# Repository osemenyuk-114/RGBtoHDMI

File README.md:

<!-- markdownlint-disable-file MD033 -->
# RGBtoHDMI Hardware Variations & Replicas

This repository contains fully open-source hardware designs, KiCad schematics, PCB layouts, manufacturing files, and Bills of Materials (BOM) for the **RGBtoHDMI** ecosystem.

**RGBtoHDMI** converts pixel-synchronous digital and analog video from vintage computers (Commodore Amiga, Atari ST, BBC Micro, Commodore 64/128, Sinclair ZX Spectrum, IBM PC MDA/CGA/EGA, Apple II, etc.) to clean HDMI using a Raspberry Pi Zero, custom bare-metal firmware, and a CPLD.

---

## 📋 Included Board Designs

### 1. CPLD Hat V6a (12-Bit Digital RGB Interface)

- **Hybrid V4/V6 Architecture:** Combines the compact design of V6 with enhanced physical durability.
- **SMD Resistor Arrays:** Uses compact `0603 x 4` convex resistor arrays (RN1–RN8) instead of the bulky through-hole arrays from the upstream V4 design.
- **Through-Hole Tactile Switches:** Uses standard, readily available 6 mm through-hole tactile pushbuttons (**Alps Alpine SKHHBVA010**) instead of SMD buttons. This change was directly motivated by real-world repair experience: when the buttons on a commercial V6 board failed, several delicate surface-mount pads tore off during desoldering, and finding identical replacement SMD switches proved difficult. THT switches make soldering, future replacements, and long-term maintenance significantly easier and more robust.
- **Quick Links:** [Schematic (PDF)](Kicad_6Bit/v6a/rgb-to-hdmi.pdf) · [Interactive BOM](Kicad_6Bit/v6a/bom/ibom.html) · [Fabrication Files](Kicad_6Bit/v6a/manufacturing/)

### 2. CPLD Hat V7a (12-Bit Digital RGB Interface, Soft Reset Option)

Based on V6a (same functionality, through-hole switches, SMD resistor arrays, same BOM) with a choice of reset wiring. Assemble **one** of the two variants:

| Variant | P4 | D3 | Reset button behavior |
| :--- | :---: | :---: | :--- |
| **A – V7 replica** | fitted | not fitted | Same as V6a: needs the Raspberry Pi reset mod (via `P4`) |
| **B – Soft reset** | not fitted | fitted | Soft reset on reset button press; no modifications to the Pi required |

- **Context:** In the upstream project, issues 5–7 are SMD-only and sold assembled; issue 6 adds series resistors on the inputs for minimal CPLD protection, and issue 7 adds the soft reset. Software reset is also possible on earlier issues by pressing SW1 & SW3.
- **Quick Links:** [Schematic (PDF)](Kicad_6Bit/v7a/rgb-to-hdmi.pdf) · [Interactive BOM](Kicad_6Bit/v7a/bom/ibom.html) · [Fabrication Files](Kicad_6Bit/v7a/manufacturing/)

### 3. HDMI Audio Adapter V2a (Audio Add-on Replica)

- **100% Open Hardware Clean-Room Reverse Engineering:** The audio add-on was previously only distributed as closed commercial hardware without public schematics or Gerber files. This replica brings the hardware back into the open-source community. See also the related [RGBtoHDMI Open Audio project](https://github.com/drdpj/RGBtoHDMI-Open-Audio).
- **Plug-and-Play:** Stacks directly onto header `P2` of the CPLD Hat to feed digital I2S audio into the Raspberry Pi Zero for embedding into the HDMI stream.
- **Quick Links:** [Schematic (PDF)](Kicad_Audio_Adapter/v2a/rgbtohdmi-audio.pdf) · [Interactive BOM](Kicad_Audio_Adapter/v2a/bom/ibom.html) · [Fabrication Files](Kicad_Audio_Adapter/v2a/manufacturing/)

### 4. Analog Board V3a (Analog RGB/YUV Add-on)

- **Cost-Optimized Design:** Compared with the upstream [V3 analog board](https://github.com/IanSB/RGBtoHDMI/tree/master/kicad_analog_6bit/V3), this revision replaces the expensive and hard-to-source `MAX9144` quad comparators with accessible, cost-effective `TLV3512DGKR` dual comparators.
- **⚠️ Untested:** This board has not been built or tested yet. The `TLV3512DGKR` comparators are much faster than the original `MAX9144` (about 6 ns vs. about 40 ns) and are comparable to the `GS8743` used on the V4 analog board (about 6 ns, 3 mV hysteresis). Build at your own risk.
- **Quick Links:** [Schematic (PDF)](Kicad_Analog_6bit/V3a/analog.pdf) · [Interactive BOM](Kicad_Analog_6bit/V3a/bom/ibom.html) · [Fabrication Files](Kicad_Analog_6bit/V3a/manufacturing/)

---

## 🏭 PCB Fabrication Guide (JLCPCB / PCBWay)

Pre-generated, verified manufacturing files (Gerbers and Excellon drill files) are available in each board's `manufacturing/` directory.

To order:

1. Zip the files in the respective board's `manufacturing/` directory.
2. Upload the `.zip` archive to your preferred PCB fabricator (e.g., JLCPCB, PCBWay, OSH Park).
3. Recommended fabrication settings:

| Parameter | Recommended Specification |
| :--- | :--- |
| **Layers** | 2 Layers |
| **Base Material** | Standard FR4 |
| **PCB Thickness** | **1.6 mm** for CPLD Hat V6a/V7a & Analog Board V3a<br>**0.8 mm** for HDMI Audio Adapter V2a |
| **Copper Weight** | 1 oz (35 µm) |
| **Surface Finish** | **ENIG** (recommended for fine-pitch packages: PCM1808 TSSOP-14, XC9572XL VQFP-44) or **Lead-Free HASL** |
| **Solder Mask** | Green (or preferred color) |
| **Silkscreen** | White |

---

## 📖 Software & Documentation

- **Firmware & Releases:** Download pre-built SD card images from the [upstream RGBtoHDMI Releases](https://github.com/IanSB/RGBtoHDMI/releases).
- **User Guide & Wiki:** Comprehensive documentation, configuration instructions, cabling guides, and supported computer profiles can be found on the [official upstream RGBtoHDMI Wiki](https://github.com/IanSB/RGBtoHDMI/wiki).
- **Audio Configuration:** In the RGBtoHDMI on-screen menu, navigate to the audio settings menu to enable HDMI audio embedding.
- **Upstream Sourcing Info:** See upstream [12-bit board BOM](https://github.com/IanSB/RGBtoHDMI/wiki/Bill-of-Materials-%2812-Bit-Board) and [HDMI Audio documentation](https://github.com/IanSB/RGBtoHDMI/wiki/Audio).

---

## 🔍 Interactive BOMs

Interactive HTML assembly guides allow you to easily highlight component placements and trace pads in your web browser:

- 🔗 **CPLD Hat V6a:** [Kicad_6Bit/v6a/bom/ibom.html](Kicad_6Bit/v6a/bom/ibom.html)
- 🔗 **CPLD Hat V7a:** [Kicad_6Bit/v7a/bom/ibom.html](Kicad_6Bit/v7a/bom/ibom.html)
- 🔗 **HDMI Audio Adapter V2a:** [Kicad_Audio_Adapter/v2a/bom/ibom.html](Kicad_Audio_Adapter/v2a/bom/ibom.html)
- 🔗 **Analog Board V3a:** [Kicad_Analog_6bit/V3a/bom/ibom.html](Kicad_Analog_6bit/V3a/bom/ibom.html)

---

## 📊 Detailed Bills of Materials (BOM)

### BOM: CPLD Hat [V6a](Kicad_6Bit/v6a) / [V7a](Kicad_6Bit/v7a)

<table width="100%">
  <thead>
    <tr>
      <th width="20%" align="left">Ref Des</th>
      <th width="35%" align="left">Value</th>
      <th width="10%" align="center">Quantity</th>
      <th width="35%" align="left">Package</th>
    </tr>
  </thead>
  <tbody>
    <tr><th colspan="4" align="left">Semiconductors</th></tr>
    <tr><td>U1</td><td>XC9572XL-VQFP44</td><td align="center">1</td><td>LQFP-44, 10 x 10 mm, 0.8 mm pitch</td></tr>
    <tr><td>D1, D2</td><td>LED 3mm</td><td align="center">2</td><td>3 mm through-hole LED</td></tr>
    <tr><td>D3 <sup>(V7a only)</sup></td><td>BAV70</td><td align="center">1</td><td>SOT-23 (see note below)</td></tr>
    <tr><th colspan="4" align="left">Resistors</th></tr>
    <tr><td>R1, R2, R3, R4, R5, R6</td><td>1K</td><td align="center">6</td><td>0603 (1608 metric), SMD</td></tr>
    <tr><td>RN1, RN2, RN3, RN4</td><td>4K7</td><td align="center">4</td><td>4 x 0603 resistor array (Convex)</td></tr>
    <tr><td>RN5, RN6, RN7, RN8</td><td>22R</td><td align="center">4</td><td>4 x 0603 resistor array (Convex)</td></tr>
    <tr><th colspan="4" align="left">Capacitors</th></tr>
    <tr><td>C1</td><td>10uF</td><td align="center">1</td><td>0805 (2012 metric), SMD</td></tr>
    <tr><td>C2, C3, C4</td><td>100nF</td><td align="center">3</td><td>0805 (2012 metric), SMD</td></tr>
    <tr><th colspan="4" align="left">Switches</th></tr>
    <tr><td>SW1, SW2, SW3, SW4</td><td>Alps Alpine<br>SKHHBVA010</td><td align="center">4</td><td>6 mm tactile pushbutton, THT</td></tr>
    <tr><th colspan="4" align="left">Sockets / Connectors</th></tr>
    <tr><td>P1</td><td>Wurth Elektronik<br>61304021821</td><td align="center">1</td><td>2 x 20, 2.54 mm socket, vertical</td></tr>
    <tr><td>P2</td><td>Samtec<br>TSW-106-08-L-D-RA</td><td align="center">1</td><td>2 x 6, 2.54 mm pin header, right-angle</td></tr>
    <tr><td>P4 <sup>(V7a: variant A only)</sup></td><td>Wurth Elektronik<br>61300211821</td><td align="center">1</td><td>1 x 2, 2.54 mm socket, vertical</td></tr>
    <tr><td>P5</td><td>Samtec<br>SLW-105-01-T-D</td><td align="center">1</td><td>2 x 5, 2.54 mm socket, vertical</td></tr>
  </tbody>
</table>

> **Note (D3, V7a only):** Fit D3 (BAV70, SOT-23) only for the soft-reset variant B, and then leave P4 unpopulated. For variant A (V7 replica) fit P4 and omit D3. V6a has neither D3 nor the variant choice (P4 is always fitted).

---

### BOM: [HDMI Audio Adapter V2a](Kicad_Audio_Adapter/v2a)

<table width="100%">
  <thead>
    <tr>
      <th width="20%" align="left">Ref Des</th>
      <th width="35%" align="left">Value</th>
      <th width="10%" align="center">Quantity</th>
      <th width="35%" align="left">Package</th>
    </tr>
  </thead>
  <tbody>
    <tr><th colspan="4" align="left">Semiconductors</th></tr>
    <tr><td>U1</td><td>PCM1808PWR</td><td align="center">1</td><td>TSSOP-14, 4.4 x 5 mm, 0.65 mm pitch</td></tr>
    <tr><td>U2</td><td>74LVC1G157</td><td align="center">1</td><td>SOT-363 (SC-70-6)</td></tr>
    <tr><td>U3, U4, U5</td><td>74LVC1G80</td><td align="center">3</td><td>SOT-353 (SC-70-5)</td></tr>
    <tr><th colspan="4" align="left">Resistors</th></tr>
    <tr><td>R1, R2</td><td>470R</td><td align="center">2</td><td>0603 (1608 metric), SMD</td></tr>
    <tr><td>R3, R5, R6</td><td>560R</td><td align="center">3</td><td>0603 (1608 metric), SMD</td></tr>
    <tr><td>R4, R7</td><td>4K7</td><td align="center">2</td><td>0603 (1608 metric), SMD</td></tr>
    <tr><th colspan="4" align="left">Capacitors</th></tr>
    <tr><td>C1, C2</td><td>1uF</td><td align="center">2</td><td>0603 (1608 metric), SMD</td></tr>
    <tr><td>C3, C4, C12</td><td>10uF</td><td align="center">3</td><td>0603 (1608 metric), SMD</td></tr>
    <tr><td>C6, C7</td><td>10nF</td><td align="center">2</td><td>0603 (1608 metric), SMD</td></tr>
    <tr><td>C5, C8, C9, C10, C11</td><td>0.1uF</td><td align="center">5</td><td>0603 (1608 metric), SMD</td></tr>
    <tr><th colspan="4" align="left">Oscillator</th></tr>
    <tr><td>Y1</td><td>12.288 MHz</td><td align="center">1</td><td>SMD oscillator, 4-pad, 3.2 x 2.5 mm</td></tr>
  </tbody>
</table>

---

### BOM: [Analog Board V3a](Kicad_Analog_6bit/V3a)

<table width="100%">
  <thead>
    <tr>
      <th width="20%" align="left">Ref Des</th>
      <th width="35%" align="left">Value</th>
      <th width="10%" align="center">Quantity</th>
      <th width="35%" align="left">Package</th>
    </tr>
  </thead>
  <tbody>
    <tr><th colspan="4" align="left">Semiconductors</th></tr>
    <tr><td>D1</td><td>MBR130LSFT1G</td><td align="center">1</td><td>SOD-123</td></tr>
    <tr><td>U1, U2, U3, U4, U5</td><td>TLV3512DGKR</td><td align="center">5</td><td>VSSOP-8 (DGK), 0.65 mm pitch</td></tr>
    <tr><td>U6</td><td>TS5A3159ADBVR</td><td align="center">1</td><td>SOT-23-6</td></tr>
    <tr><td>U7</td><td>74LVC4066</td><td align="center">1</td><td>SOIC-14, 3.9 x 8.7 mm, 1.27 mm pitch</td></tr>
    <tr><td>U8</td><td>MAX5259EEE+</td><td align="center">1</td><td>QSOP-16, 3.9 x 4.9 mm, 0.635 mm pitch</td></tr>
    <tr><td>U9</td><td>MCP1754S-3302xCB</td><td align="center">1</td><td>SOT-23</td></tr>
    <tr><th colspan="4" align="left">Resistors</th></tr>
    <tr><td>R1</td><td>470R</td><td align="center">1</td><td>0805 (2012 metric), SMD</td></tr>
    <tr><td>R2, R3, R4</td><td>1K</td><td align="center">3</td><td>0805 (2012 metric), SMD</td></tr>
    <tr><td>R5</td><td>10K</td><td align="center">1</td><td>0805 (2012 metric), SMD</td></tr>
    <tr><td>R6, R7, R8</td><td>47K</td><td align="center">3</td><td>0805 (2012 metric), SMD</td></tr>
    <tr><td>R9, R10, R11</td><td>75R</td><td align="center">3</td><td>0805 (2012 metric), SMD</td></tr>
    <tr><th colspan="4" align="left">Capacitors</th></tr>
    <tr><td>C1, C2, C3, C4, C5</td><td>100nF</td><td align="center">5</td><td>0805 (2012 metric), SMD</td></tr>
    <tr><td>C6, C7, C8, C9</td><td>10uF</td><td align="center">4</td><td>0805 (2012 metric), SMD</td></tr>
    <tr><th colspan="4" align="left">Sockets / Connectors</th></tr>
    <tr><td>P1</td><td>Samtec<br>SSW-106-02-T-D-RA</td><td align="center">1</td><td>2 x 6, 2.54 mm socket, right-angle</td></tr>
    <tr><td>P2</td><td>Samtec<br>TLW-104-06-T-S</td><td align="center">1</td><td>1 x 4, 2.54 mm pin header, vertical</td></tr>
    <tr><td>P4</td><td>IDC 6 pin</td><td align="center">1</td><td>2 x 3, 2.54 mm pin header, vertical</td></tr>
    <tr><td>P6, P7</td><td>Samtec<br>TLW-101-06-T-S</td><td align="center">2</td><td>1 x 1, 2.54 mm pin header, vertical</td></tr>
  </tbody>
</table>

---

## 📜 License & Acknowledgments

- This project is distributed under the **GNU General Public License v3.0 (GPL-3.0)**. See the [LICENSE](LICENSE) file for details.
- Original RGBtoHDMI design by David Banks ([hoglet67](https://github.com/hoglet67/RGBtoHDMI)).
- Extended development and maintenance by [IanSB](https://github.com/IanSB/RGBtoHDMI).
- Audio reverse-engineering inspiration and insights from [drdpj/RGBtoHDMI-Open-Audio](https://github.com/drdpj/RGBtoHDMI-Open-Audio).

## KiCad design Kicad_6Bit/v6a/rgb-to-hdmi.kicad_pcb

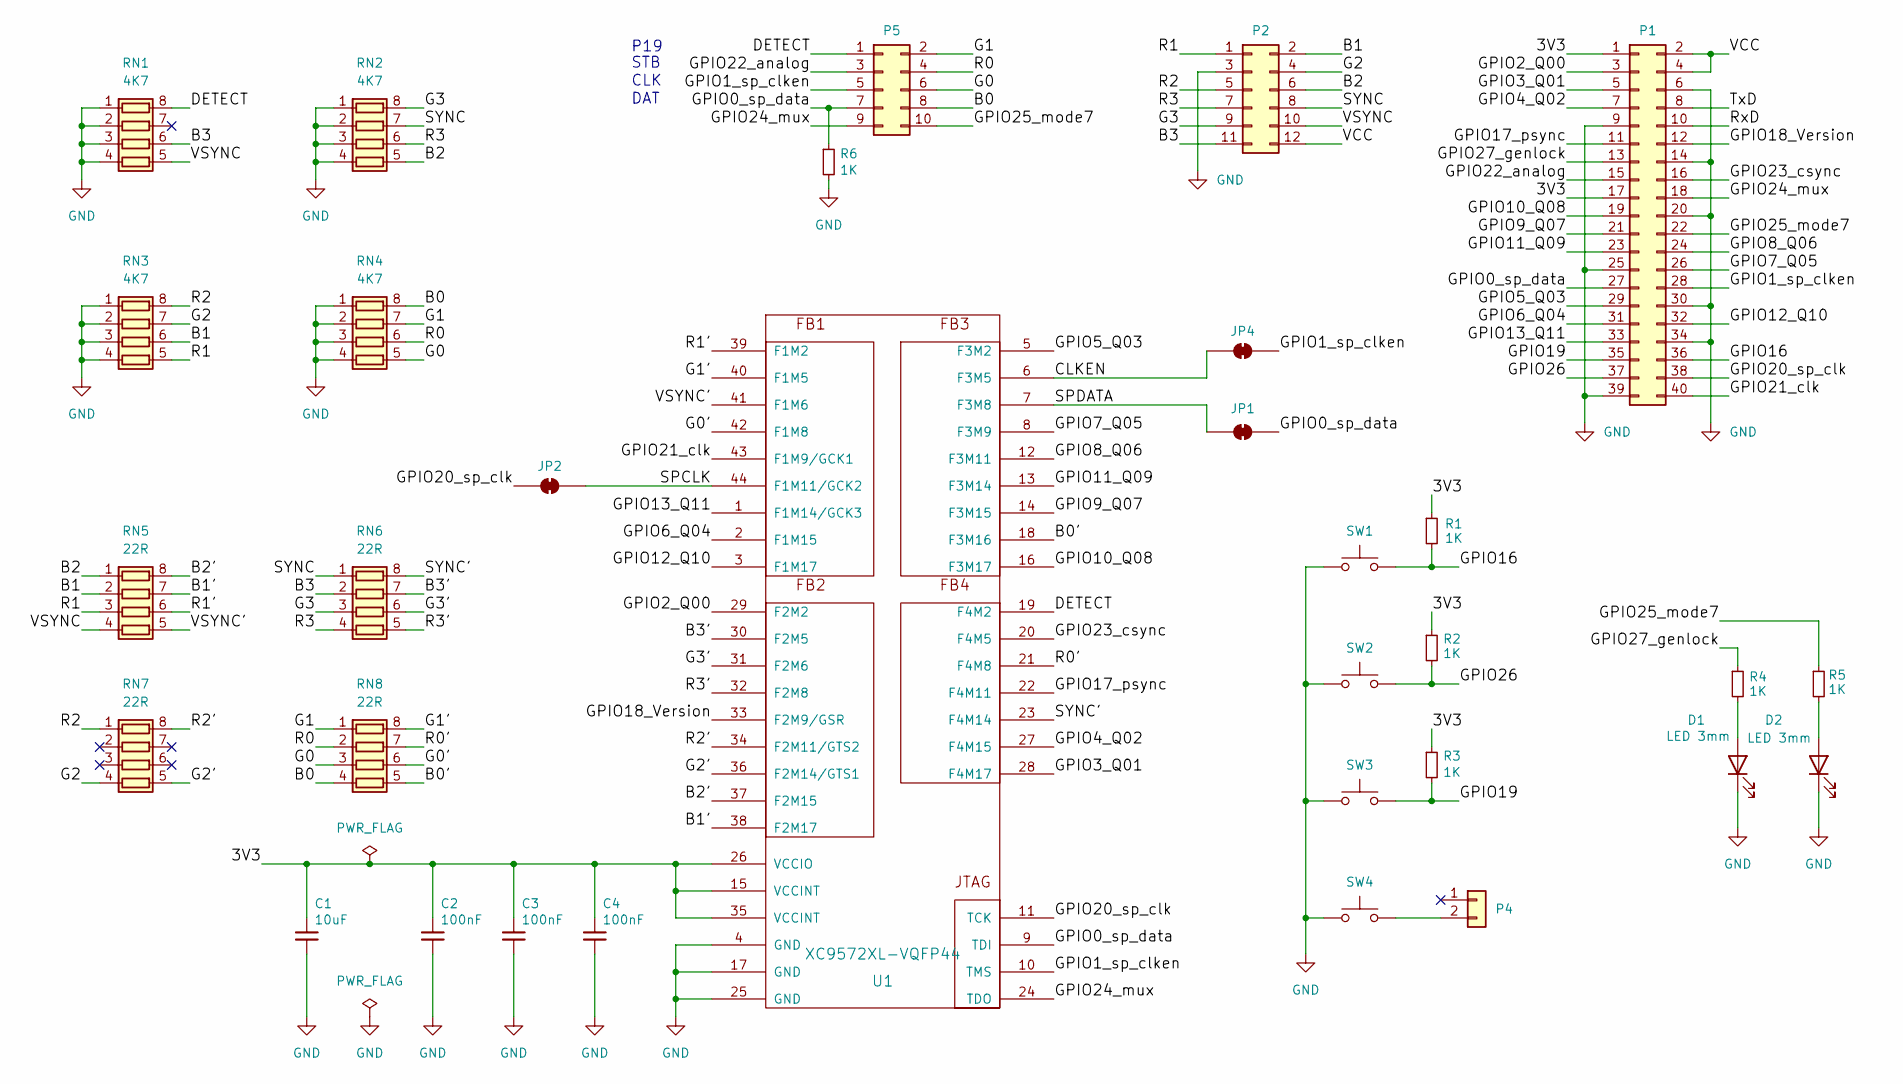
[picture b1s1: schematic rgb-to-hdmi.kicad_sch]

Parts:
C1: 10uF; C_0805_2012Metric_Pad1.18x1.45mm_HandSolder
C2, C3, C4: 100nF; C_0805_2012Metric_Pad1.18x1.45mm_HandSolder
D1, D2: LED 3mm; LED_D3.0mm
JP1, JP2, JP4: Solder Jumper 2 Bridged; SolderJumper-2_P1.3mm_Bridged_RoundedPad1.0x1.5mm
P1: Wurth Elektronik 61304021821; PinSocket_2x20_P2.54mm_Vertical
P2: Samtec TSW-106-08-L-D-RA; PinHeader_2x06_P2.54mm_Horizontal
P4: Wurth Elektronik 61300211821; PinSocket_1x02_P2.54mm_Vertical
P5: Samtec SLW-105-01-T-D; PinSocket_2x05_P2.54mm_Vertical
R1, R2, R3, R4, R5, R6: 1K; R_0603_1608Metric_Pad0.98x0.95mm_HandSolder
RN1, RN2, RN3, RN4: 4K7; R_Array_Convex_4x0603
RN5, RN6, RN7, RN8: 22R; R_Array_Convex_4x0603
SW1, SW2, SW3, SW4: Alps Alpine SKHHBVA010; SW_PUSH_6mm_H7.3mm
U1: XC9572XL-VQFP44; LQFP-44_10x10mm_P0.8mm

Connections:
/3V3: C1.1, C2.1, C3.1, C4.1, P1.1, P1.17, R1.1, R2.1, R3.1, U1.15 (VCCINT), U1.26 (VCCIO), U1.35 (VCCINT)
/B0: P5.8, RN4.8 (R1.2), RN8.4 (R4.1)
/B0': RN8.5 (R4.2), U1.18 (F3M16)
/B1: P2.2, RN3.6 (R3.2), RN5.2 (R2.1)
/B1': RN5.7 (R2.2), U1.38 (F2M17)
/B2: P2.6, RN2.5 (R4.2), RN5.1 (R1.1)
/B2': RN5.8 (R1.2), U1.37 (F2M15)
/B3: P2.11, RN1.6 (R3.2), RN6.2 (R2.1)
/B3': RN6.7 (R2.2), U1.30 (F2M5)
/CLKEN: JP4.2 (B), U1.6 (F3M5)
/DETECT: P5.1, RN1.8 (R1.2), U1.19 (F4M2)
/G0: P5.6, RN4.5 (R4.2), RN8.3 (R3.1)
/G0': RN8.6 (R3.2), U1.42 (F1M8)
/G1: P5.2, RN4.7 (R2.2), RN8.1 (R1.1)
/G1': RN8.8 (R1.2), U1.40 (F1M5)
/G2: P2.4, RN3.7 (R2.2), RN7.4 (R4.1)
/G2': RN7.5 (R4.2), U1.36 (F2M14/GTS1)
/G3: P2.9, RN2.8 (R1.2), RN6.3 (R3.1)
/G3': RN6.6 (R3.2), U1.31 (F2M6)
/GPIO0_sp_data: JP1.1 (A), P1.27, P5.7, R6.1, U1.9 (TDI)
/GPIO1_sp_clken: JP4.1 (A), P1.28, P5.5, U1.10 (TMS)
/GPIO2_Q00: P1.3, U1.29 (F2M2)
/GPIO3_Q01: P1.5, U1.28 (F4M17)
/GPIO4_Q02: P1.7, U1.27 (F4M15)
/GPIO5_Q03: P1.29, U1.5 (F3M2)
/GPIO6_Q04: P1.31, U1.2 (F1M15)
/GPIO7_Q05: P1.26, U1.8 (F3M9)
/GPIO8_Q06: P1.24, U1.12 (F3M11)
/GPIO9_Q07: P1.21, U1.14 (F3M15)
/GPIO10_Q08: P1.19, U1.16 (F3M17)
/GPIO11_Q09: P1.23, U1.13 (F3M14)
/GPIO12_Q10: P1.32, U1.3 (F1M17)
/GPIO13_Q11: P1.33, U1.1 (F1M14/GCK3)
/GPIO16: P1.36, R1.2, SW1.2
/GPIO17_psync: P1.11, U1.22 (F4M11)
/GPIO18_Version: P1.12, U1.33 (F2M9/GSR)
/GPIO19: P1.35, R3.2, SW3.2
/GPIO20_sp_clk: JP2.1 (A), P1.38, U1.11 (TCK)
/GPIO21_clk: P1.40, U1.43 (F1M9/GCK1)
/GPIO22_analog: P1.15, P5.3
/GPIO23_csync: P1.16, U1.20 (F4M5)
/GPIO24_mux: P1.18, P5.9, U1.24 (TDO)
/GPIO25_mode7: P1.22, P5.10, R5.1
/GPIO26: P1.37, R2.2, SW2.2
/GPIO27_genlock: P1.13, R4.1
/R0: P5.4, RN4.6 (R3.2), RN8.2 (R2.1)
/R0': RN8.7 (R2.2), U1.21 (F4M8)
/R1: P2.1, RN3.5 (R4.2), RN5.3 (R3.1)
/R1': RN5.6 (R3.2), U1.39 (F1M2)
/R2: P2.5, RN3.8 (R1.2), RN7.1 (R1.1)
/R2': RN7.8 (R1.2), U1.34 (F2M11/GTS2)
/R3: P2.7, RN2.6 (R3.2), RN6.4 (R4.1)
/R3': RN6.5 (R4.2), U1.32 (F2M8)
/RxD: P1.10
/SPCLK: JP2.2 (B), U1.44 (F1M11/GCK2)
/SPDATA: JP1.2 (B), U1.7 (F3M8)
/SYNC: P2.8, RN2.7 (R2.2), RN6.1 (R1.1)
/SYNC': RN6.8 (R1.2), U1.23 (F4M14)
/TxD: P1.8
/VCC: P1.2, P1.4, P2.12
/VSYNC: P2.10, RN1.5 (R4.2), RN5.4 (R4.1)
/VSYNC': RN5.5 (R4.2), U1.41 (F1M6)
GND: C1.2, C2.2, C3.2, C4.2, D1.1 (K), D2.1 (K), P1.6, P1.9, P1.14, P1.20, P1.25, P1.30, P1.34, P1.39, P2.3, R6.2, RN1.1 (R1.1), RN1.2 (R2.1), RN1.3 (R3.1), RN1.4 (R4.1), RN2.1 (R1.1), RN2.2 (R2.1), RN2.3 (R3.1), RN2.4 (R4.1), RN3.1 (R1.1), RN3.2 (R2.1), RN3.3 (R3.1), RN3.4 (R4.1), RN4.1 (R1.1), RN4.2 (R2.1), RN4.3 (R3.1), RN4.4 (R4.1), SW1.1, SW2.1, SW3.1, SW4.1, U1.4 (GND), U1.17 (GND), U1.25 (GND)
unnamed: D1.2 (A), R4.2
unnamed: D2.2 (A), R5.2
unnamed: P4.2 (Pin_2_2), SW4.2

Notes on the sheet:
DAT
P19
CLK
STB

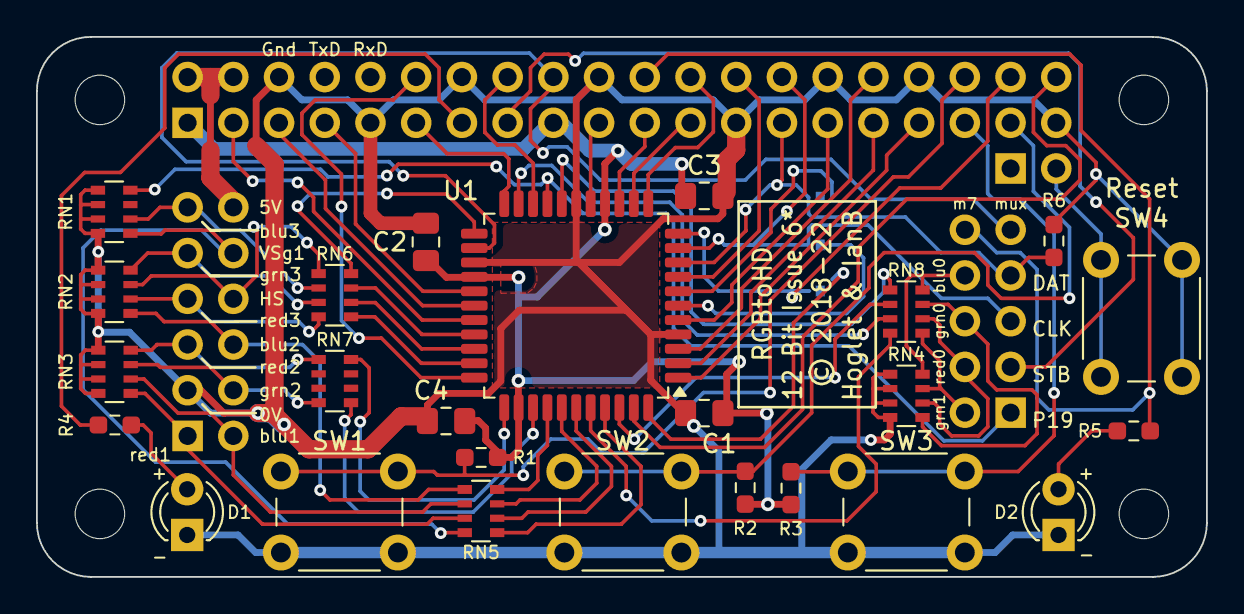
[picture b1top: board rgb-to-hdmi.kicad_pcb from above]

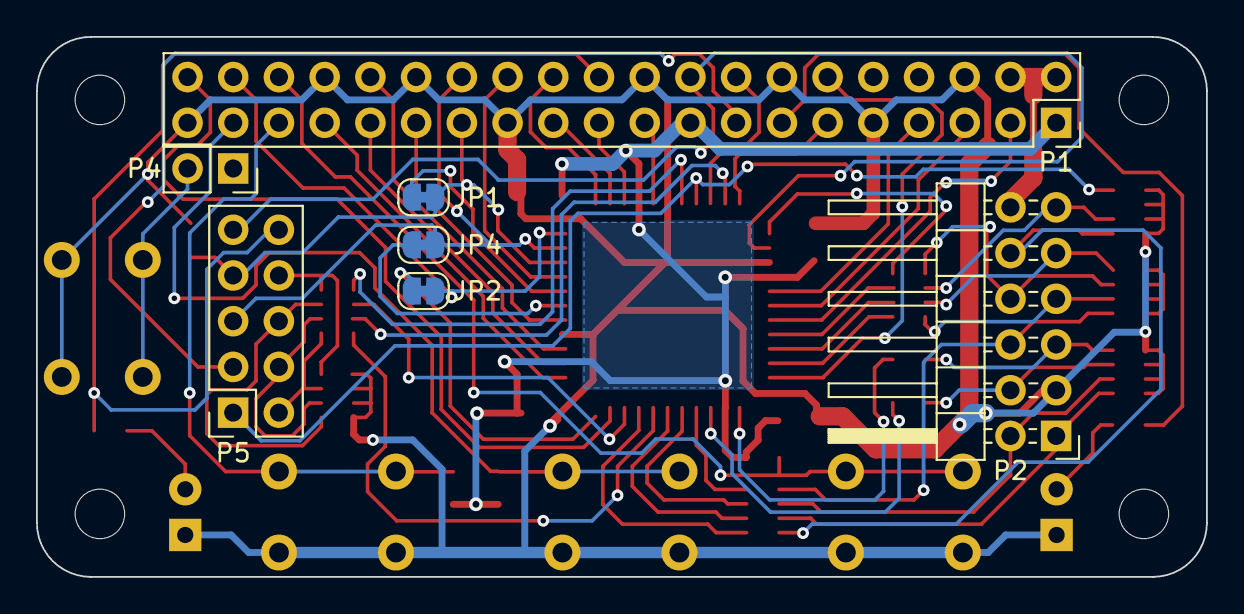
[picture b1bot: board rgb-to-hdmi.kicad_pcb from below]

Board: 2 copper layers, 65.0 x 30.0 mm, 32 parts (7 on the bottom side), 64 nets.

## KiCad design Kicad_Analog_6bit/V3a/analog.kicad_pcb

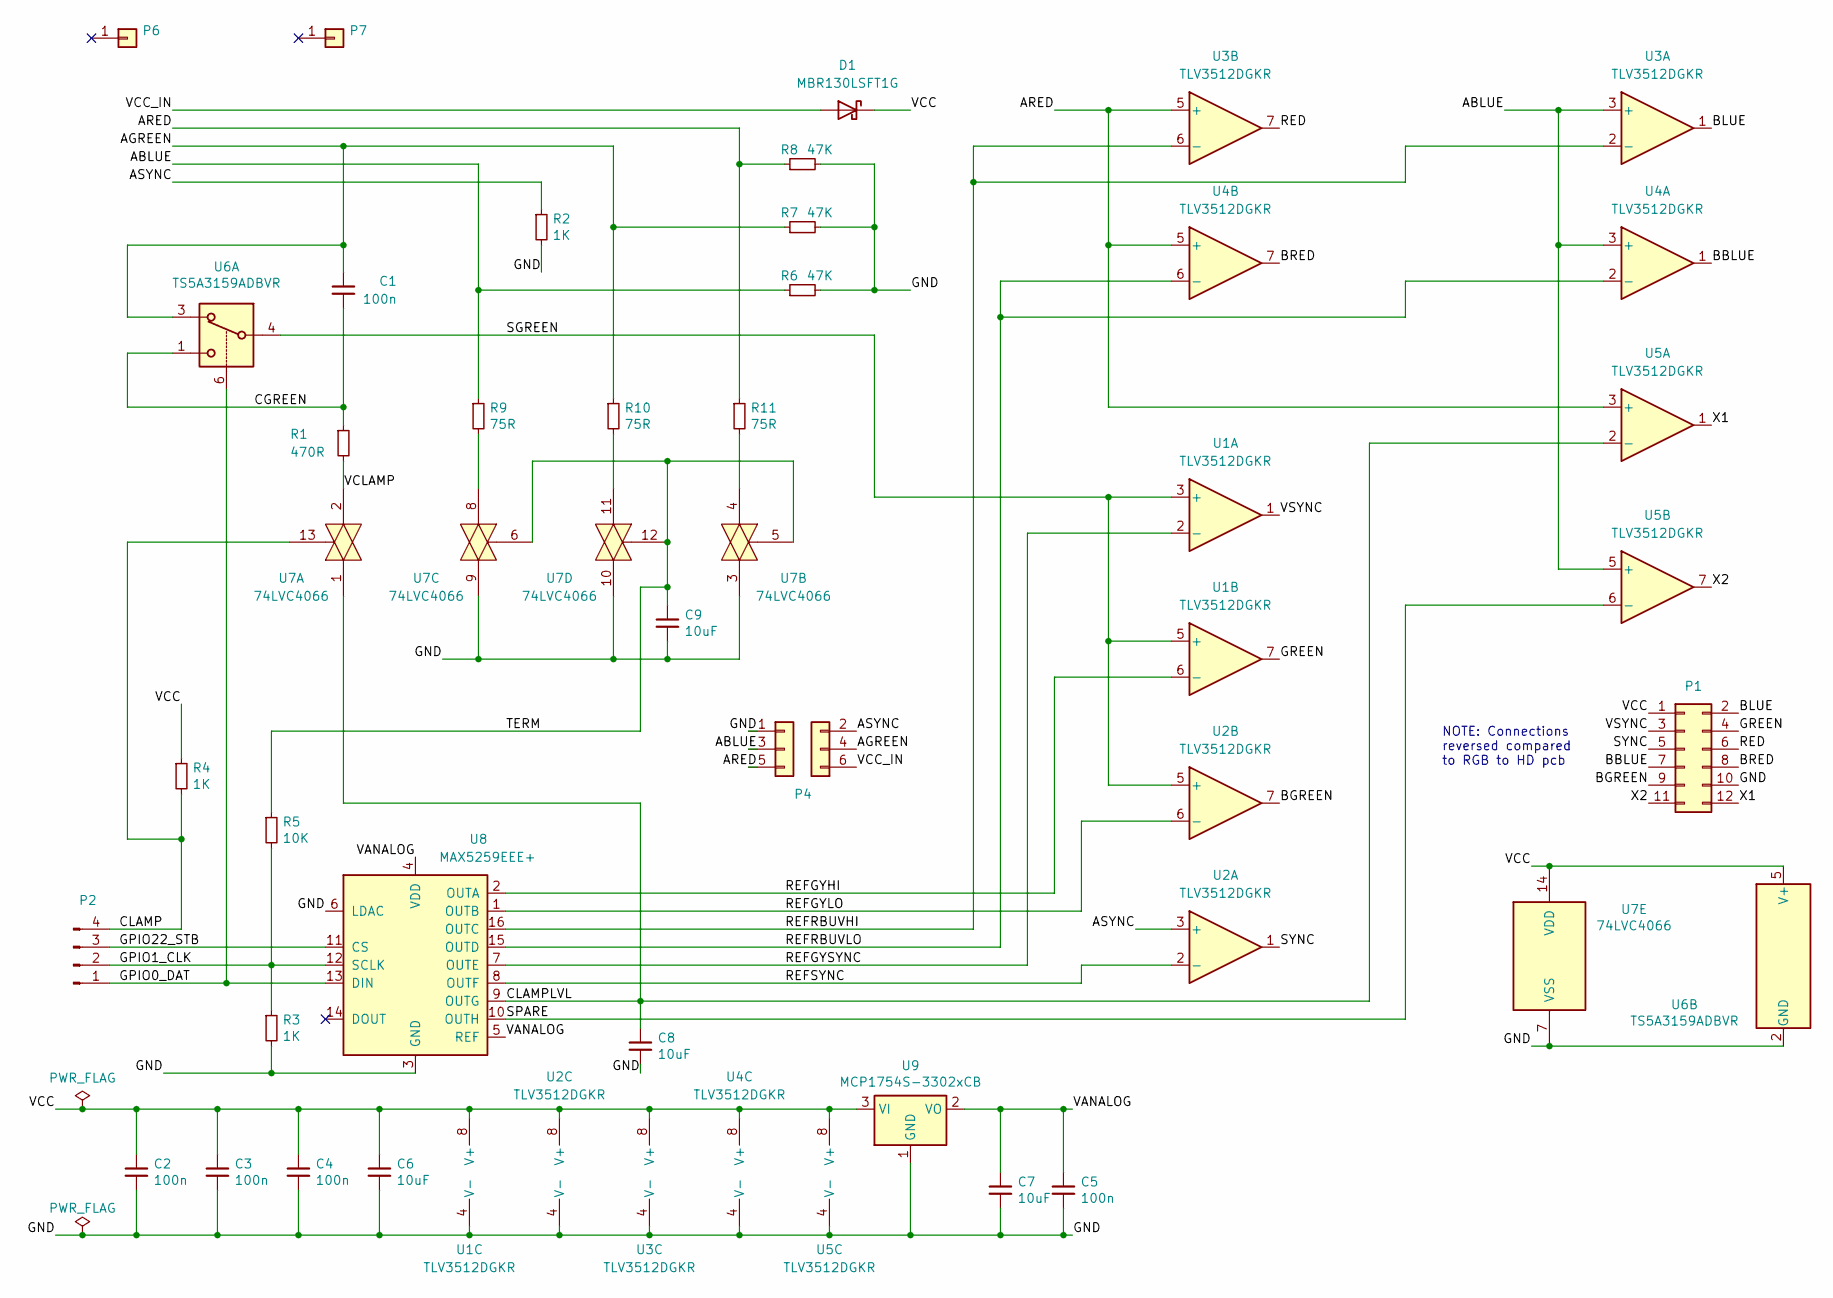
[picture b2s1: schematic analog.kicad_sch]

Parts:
C1, C2, C3, C4, C5: 100n; C_0805_2012Metric_Pad1.18x1.45mm_HandSolder
C6, C7, C8, C9: 10uF; C_0805_2012Metric_Pad1.18x1.45mm_HandSolder
D1: MBR130LSFT1G; D_SOD-123
P1: Samtec SSW-106-02-T-D-RA; PinSocket_2x06_P2.54mm_Horizontal
P2: Samtec TLW-104-06-T-S; PinHeader_1x04_P2.54mm_Vertical
P4: IDC 6pin; Harwin_M20-89003xx_1x03_P2.54mm_Horizontal_Custom_ODD2
P5: Conn_01x03_EVEN; Harwin_M20-89003xx_1x03_P2.54mm_Horizontal_Custom_EVEN2
P6, P7: Samtec TLW-101-06-T-S; PinHeader_1x01_P2.54mm_Vertical
R1: 470R; R_0805_2012Metric_Pad1.20x1.40mm_HandSolder
R2, R3, R4: 1K; R_0805_2012Metric_Pad1.20x1.40mm_HandSolder
R5: 10K; R_0805_2012Metric_Pad1.20x1.40mm_HandSolder
R6, R7, R8: 47K; R_0805_2012Metric_Pad1.20x1.40mm_HandSolder
R9, R10, R11: 75R; R_0805_2012Metric_Pad1.20x1.40mm_HandSolder
U1, U2, U3, U4, U5: TLV3512DGKR; SSOP-8_2.95x2.8mm_P0.65mm
U6: TS5A3159ADBVR; SOT-23-6_Handsoldering
U7: 74LVC4066; SOIC-14_3.9x8.7mm_P1.27mm
U8: MAX5259EEE+; QSOP-16_3.9x4.9mm_P0.635mm
U9: MCP1754S-3302xCB; SOT-23_Handsoldering

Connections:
/ABLUE: P4.3, R6.1, R9.1, U3.3 (+), U4.3 (+), U5.5 (+)
/AGREEN: C1.1, P5.4, R7.1, R10.1, U6.3
/ARED: P4.5, R8.1, R11.1, U3.5 (+), U4.5 (+), U5.3 (+)
/ASYNC: P5.2, R2.1, U2.3 (+)
/BBLUE: P1.7, U4.1
/BGREEN: P1.9, U2.7
/BLUE: P1.2, U3.1
/BRED: P1.8, U4.7
/CGREEN: C1.2, R1.1, U6.1
/CLAMP: P2.4, R4.2, U7.13
/CLAMPLVL: C8.1, U5.2 (-), U7.1, U8.9 (OUTG)
/GND: C2.2, C3.2, C4.2, C5.2, C6.2, C7.2, C8.2, C9.2, P1.10, P4.1, R2.2, R3.2, R6.2, R7.2, R8.2, U1.4 (V-), U2.4 (V-), U3.4 (V-), U4.4 (V-), U5.4 (V-), U6.2 (GND), U7.3, U7.7 (VSS), U7.9, U7.10, U8.3 (GND), U8.6 (LDAC), U9.1 (GND)
/GPIO0_DAT: P2.1, U6.6, U8.13 (DIN)
/GPIO1_CLK: P2.2, R3.1, R5.2, U8.12 (SCLK)
/GPIO22_STB: P2.3, U8.11 (CS)
/GREEN: P1.4, U1.7
/RED: P1.6, U3.7
/REFGYHI: U1.6 (-), U8.2 (OUTA)
/REFGYLO: U2.6 (-), U8.1 (OUTB)
/REFGYSYNC: U1.2 (-), U8.7 (OUTE)
/REFRBUVHI: U3.2 (-), U3.6 (-), U8.16 (OUTC)
/REFRBUVLO: U4.2 (-), U4.6 (-), U8.15 (OUTD)
/REFSYNC: U2.2 (-), U8.8 (OUTF)
/SGREEN: U1.3 (+), U1.5 (+), U2.5 (+), U6.4
/SPARE: U5.6 (-), U8.10 (OUTH)
/SYNC: P1.5, U2.1
/TERM: C9.1, R5.1, U7.5, U7.6, U7.12
/VANALOG: C5.1, C7.1, U8.4 (VDD), U8.5 (REF), U9.2 (VO)
/VCC: C2.1, C3.1, C4.1, C6.1, D1.1 (K), P1.1, R4.1, U1.8 (V+), U2.8 (V+), U3.8 (V+), U4.8 (V+), U5.8 (V+), U6.5 (V+), U7.14 (VDD), U9.3 (VI)
/VCC_IN: D1.2 (A), P5.6
/VCLAMP: R1.2, U7.2
/VSYNC: P1.3, U1.1
/X1: P1.12, U5.1
/X2: P1.11, U5.7
unnamed: R9.2, U7.8
unnamed: R10.2, U7.11
unnamed: R11.2, U7.4

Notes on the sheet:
NOTE: Connections reversed compared to RGB to HD pcb

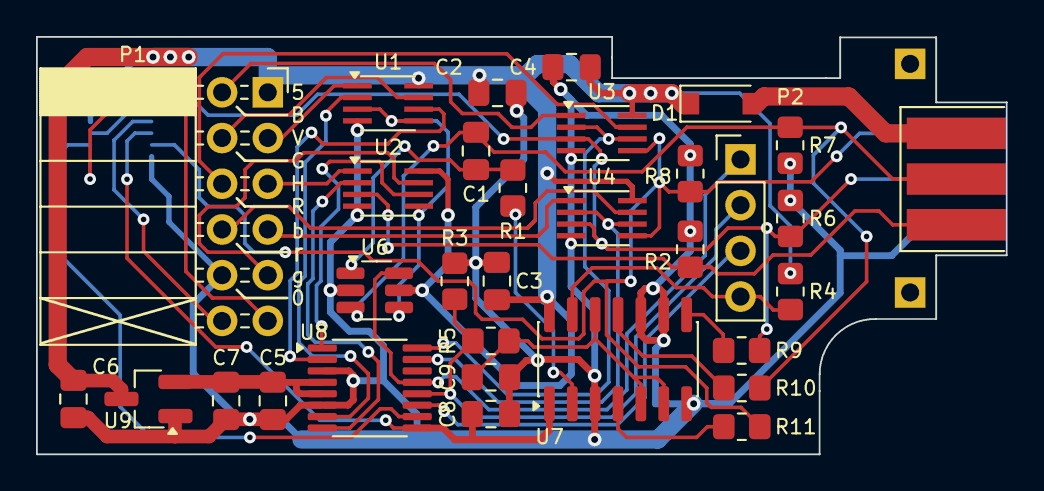
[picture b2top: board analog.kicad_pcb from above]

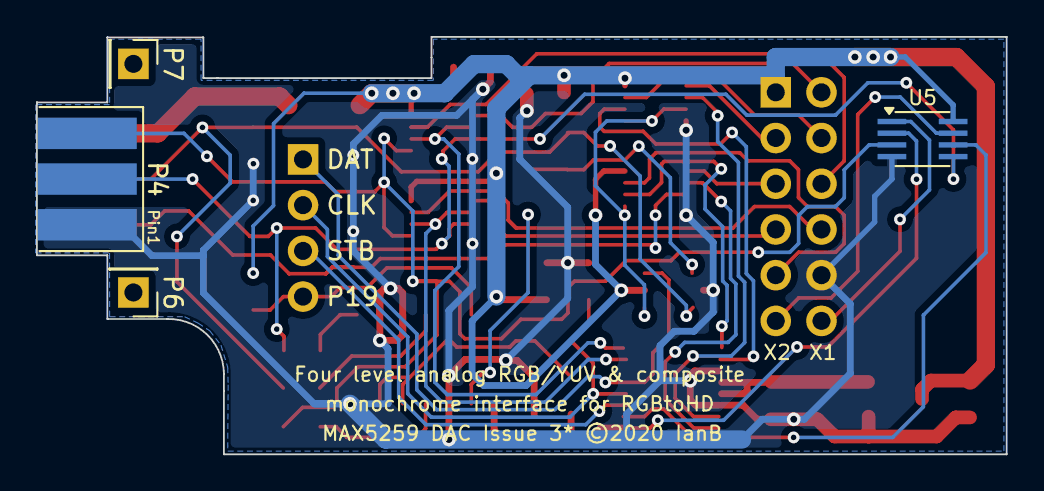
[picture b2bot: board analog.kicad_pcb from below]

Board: 2 copper layers, 53.9 x 23.2 mm, 36 parts (4 on the bottom side), 37 nets.

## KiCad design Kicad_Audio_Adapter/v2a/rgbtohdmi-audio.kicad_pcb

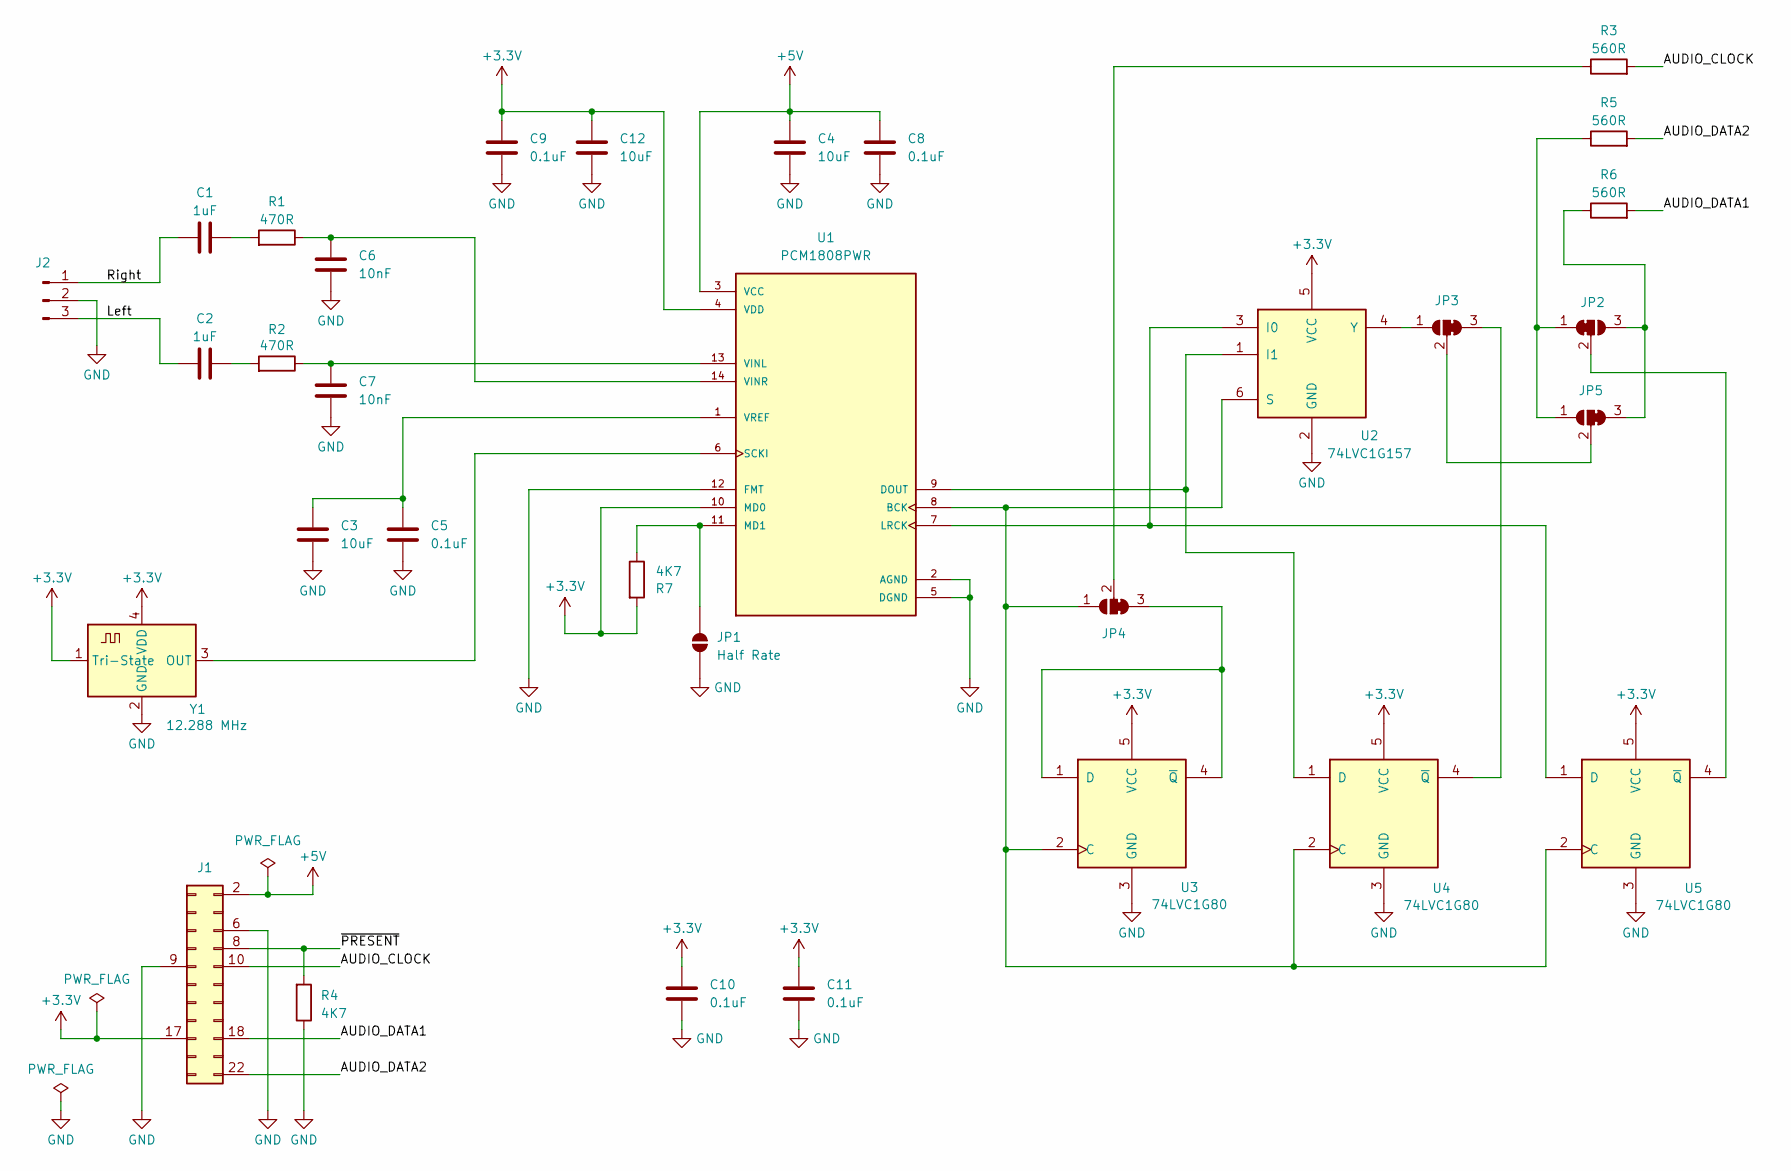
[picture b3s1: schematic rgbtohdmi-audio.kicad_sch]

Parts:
C1, C2: 1uF; C_0603_1608Metric_Pad1.08x0.95mm_HandSolder
C3, C4, C12: 10uF; C_0603_1608Metric_Pad1.08x0.95mm_HandSolder
C5, C8, C9, C10, C11: 0.1uF; C_0603_1608Metric_Pad1.08x0.95mm_HandSolder
C6, C7: 10nF; C_0603_1608Metric_Pad1.08x0.95mm_HandSolder
J1: Conn_02x11_Odd_Even; PinHeader_2x11_P2.54mm_Vertical
J2: Conn_01x03; SolderWirePad_1x03_SMD_2x4mm
JP1: Half Rate; SolderJumper-2_P1.3mm_Open_RoundedPad1.0x1.5mm
JP2: SolderJumper_3_Bridged12; SolderJumper-3_P1.3mm_Bridged12_RoundedPad1.0x1.5mm
JP3, JP4, JP5: SolderJumper-3_P1.3mm_Bridged23_RoundedPad1.0x1.5mm
R1, R2: 470R; R_0603_1608Metric_Pad0.98x0.95mm_HandSolder
R3, R5, R6: 560R; R_0603_1608Metric_Pad0.98x0.95mm_HandSolder
R4, R7: 4K7; R_0603_1608Metric_Pad0.98x0.95mm_HandSolder
U1: PCM1808PWR; TSSOP-14_4.4x5mm_P0.65mm; PARTREV B
U2: 74LVC1G157; SOT-363_SC-70-6
U3, U4, U5: 74LVC1G80; SOT-353_SC-70-5
Y1: 12.288 MHz; Oscillator_SMD_SeikoEpson_SG8002CE-4Pin_3.2x2.5mm

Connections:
+3.3V: C9.1, C10.1, C11.1, C12.1, J1.17, R7.2, U1.4 (VDD), U1.10 (MD0), U2.5 (VCC), U3.5 (VCC), U4.5 (VCC), U5.5 (VCC), Y1.1 (Tri-State), Y1.4 (VDD)
+5V: C4.1, C8.1, J1.2, U1.3 (VCC)
/AUDIO_CLOCK: J1.10, R3.2
/AUDIO_DATA1: J1.18, R6.2
/AUDIO_DATA2: J1.22, R5.2
/Left: C2.2, J2.3
/Right: C1.2, J2.1
/~PRESENT: J1.8, R4.2
GND: C3.2, C4.2, C5.2, C6.2, C7.2, C8.2, C9.2, C10.2, C11.2, C12.2, J1.6, J1.9, J2.2, JP1.2 (B), R4.1, U1.2 (AGND), U1.5 (DGND), U1.12 (FMT), U2.2 (GND), U3.3 (GND), U4.3 (GND), U5.3 (GND), Y1.2 (GND)
unnamed: C1.1, R1.2
unnamed: C2.1, R2.2
unnamed: JP1.1 (A), R7.1, U1.11 (MD1)
unnamed: JP2.1 (A), JP5.1 (A), R5.1
unnamed: JP2.3 (B), JP5.3 (B), R6.1
unnamed: JP2.2 (C), U5.4 (~Q)
unnamed: JP3.1 (A), U2.4 (Y)
unnamed: JP3.3 (B), U4.4 (~Q)
unnamed: JP3.2 (C), JP5.2 (C)
unnamed: JP4.1 (A), U1.8 (BCK), U2.6 (S), U3.2 (C), U4.2 (C), U5.2 (C)
unnamed: JP4.3 (B), U3.1 (D), U3.4 (~Q)
unnamed: JP4.2 (C), R3.1
unnamed: U1.9 (DOUT), U2.1 (I1), U4.1 (D)
unnamed: U1.7 (LRCK), U2.3 (I0), U5.1 (D)
unnamed: U1.6 (SCKI), Y1.3 (OUT)
unnamed: C7.1, R2.1, U1.13 (VINL)
unnamed: C6.1, R1.1, U1.14 (VINR)
unnamed: C3.1, C5.1, U1.1 (VREF)

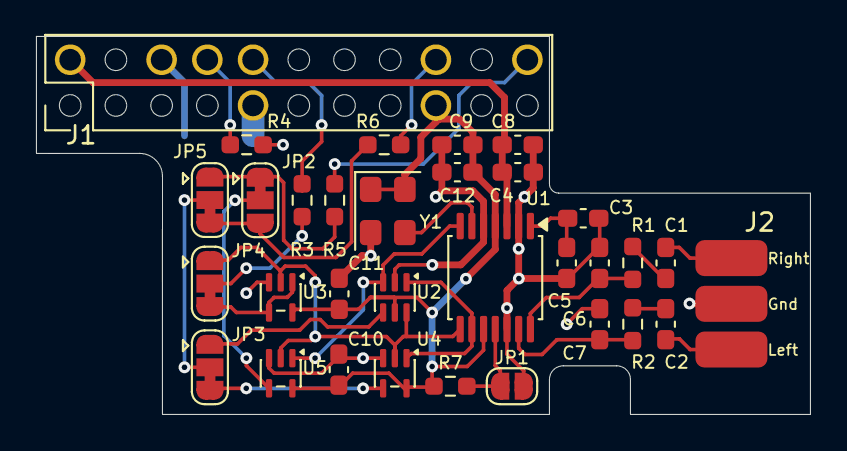
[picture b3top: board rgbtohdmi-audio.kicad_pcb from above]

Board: 2 copper layers, 43.0 x 21.0 mm, 32 parts (0 on the bottom side), 27 nets.

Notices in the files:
Kicad_6Bit/v6a/rgb-to-hdmi.kicad_pcb:
© 2018-22
Kicad_Analog_6bit/V3a/analog.kicad_pcb:
MAX5259 DAC Issue 3* ©2020 IanB
README.md:
License: GPL v3
